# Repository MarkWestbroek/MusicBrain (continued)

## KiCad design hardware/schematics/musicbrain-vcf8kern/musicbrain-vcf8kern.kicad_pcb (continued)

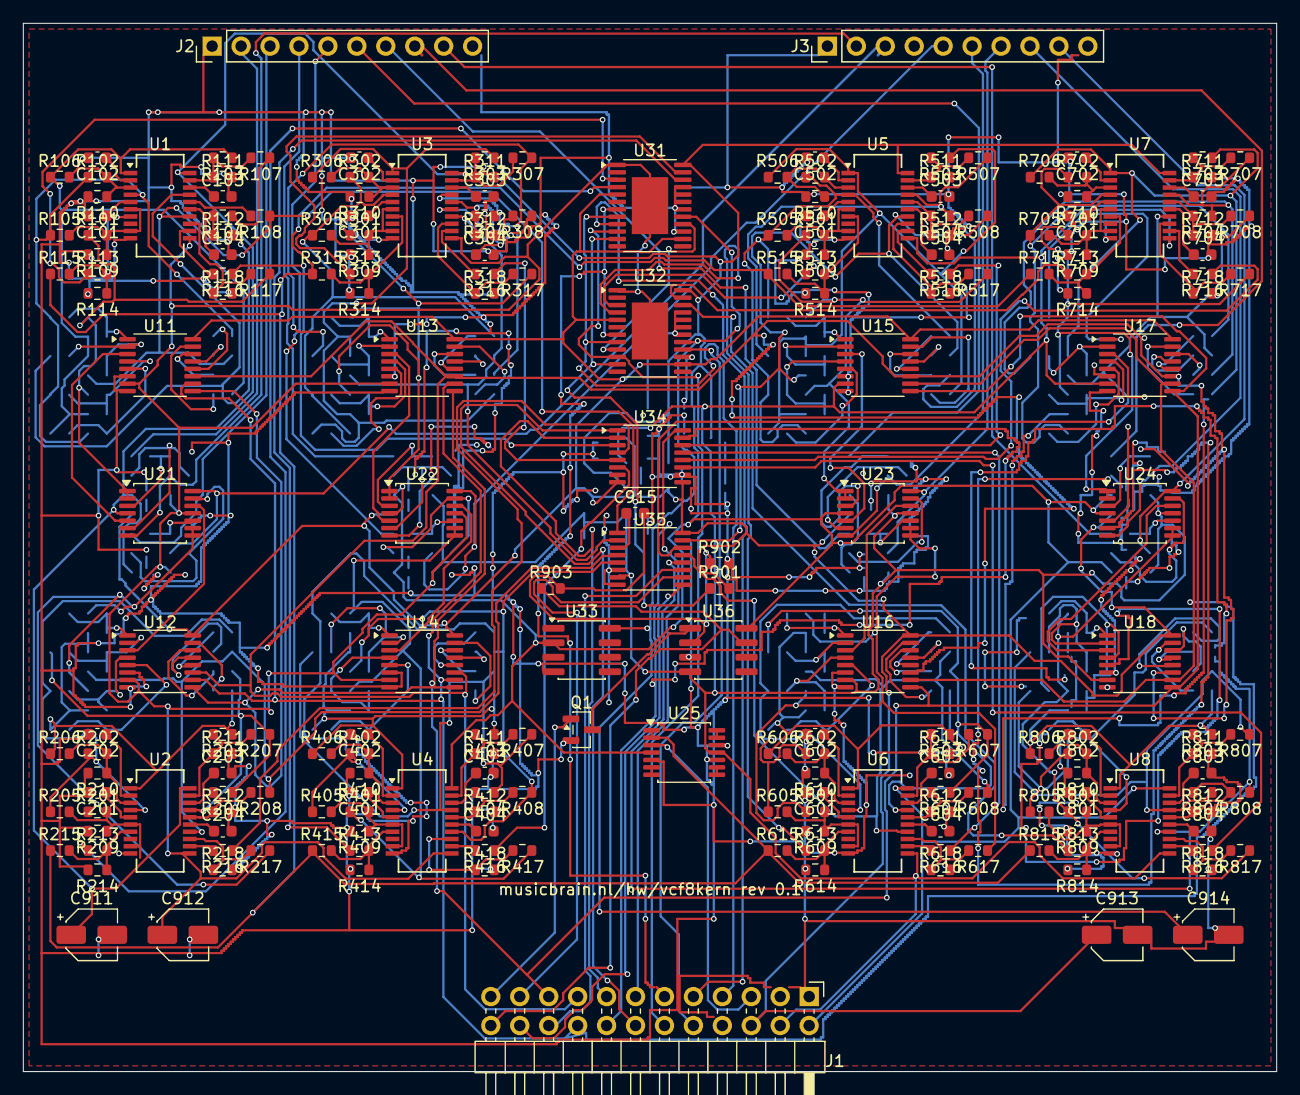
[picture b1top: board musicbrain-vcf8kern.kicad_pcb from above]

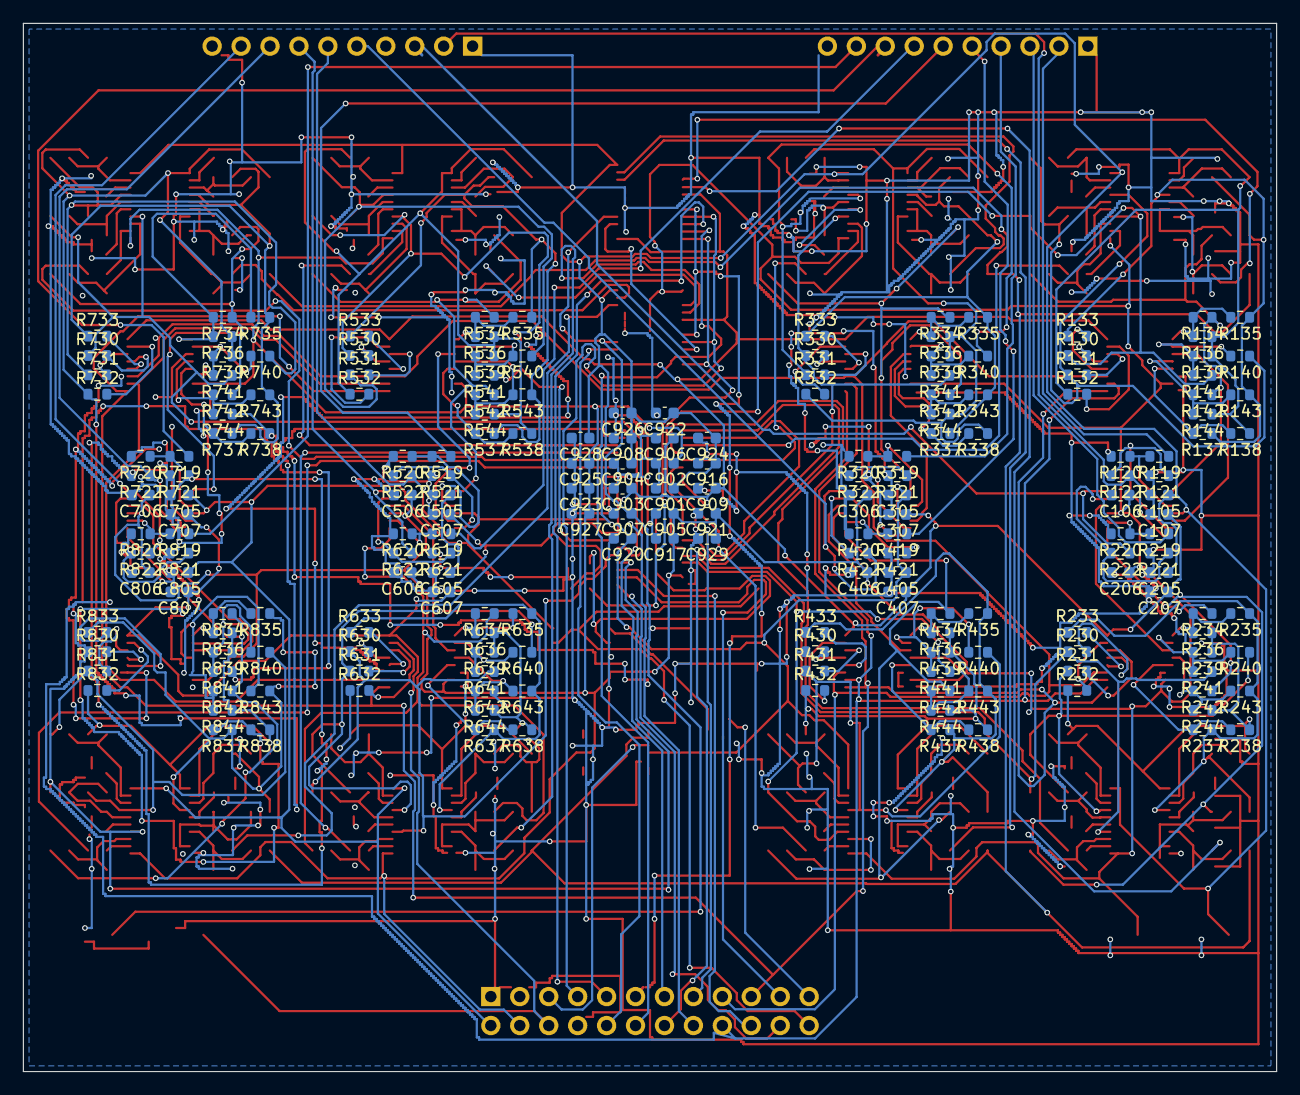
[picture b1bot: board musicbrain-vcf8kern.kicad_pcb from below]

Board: 4 copper layers, 110.0 x 92.0 mm, 412 parts (197 on the bottom side), 280 nets.

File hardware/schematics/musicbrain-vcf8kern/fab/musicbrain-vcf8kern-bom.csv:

"Comment","Designator","Footprint","LCSC Part #"
"1n","C101,C102,C103,C104,C201,C202,C203,C204,C301,C302,C303,C304,C401,C402,C403,C404,C501,C502,C503,C504,C601,C602,C603,C604,C701,C702,C703,C704,C801,C802,C803,C804","C_0603_1608Metric",""
"100n","C105,C106,C107,C205,C206,C207,C305,C306,C307,C405,C406,C407,C505,C506,C507,C605,C606,C607,C705,C706,C707,C805,C806,C807,C901,C902,C903,C904,C905,C906,C907,C908,C909,C916,C917,C920,C921,C922,C923,C924,C925,C926,C927,C928,C929","C_0603_1608Metric",""
"10u","C911,C912,C913,C914","CP_Elec_4x5.3","C3343"
"10n","C915","C_0603_1608Metric",""
"KERNSLOT (2x12)","J1","",""
"AUDIO IN","J2","",""
"AUDIO UIT","J3","",""
"2N7002","Q1","SOT-23",""
"15k","R101,R102,R103,R104,R105,R106,R107,R108,R121,R201,R202,R203,R204,R205,R206,R207,R208,R221,R301,R302,R303,R304,R305,R306,R307,R308,R321,R401,R402,R403,R404,R405,R406,R407,R408,R421,R501,R502,R503,R504,R505,R506,R507,R508,R521,R601,R602,R603,R604,R605,R606,R607,R608,R621,R701,R702,R703,R704,R705,R706,R707,R708,R721,R801,R802,R803,R804,R805,R806,R807,R808,R821","R_0603_1608Metric",""
"200R","R109,R110,R111,R112,R209,R210,R211,R212,R309,R310,R311,R312,R409,R410,R411,R412,R509,R510,R511,R512,R609,R610,R611,R612,R709,R710,R711,R712,R809,R810,R811,R812","R_0603_1608Metric",""
"54.9k","R113,R213,R313,R413,R513,R613,R713,R813","R_0603_1608Metric",""
"1k","R114,R118,R214,R218,R314,R318,R414,R418,R514,R518,R614,R618,R714,R718,R814,R818","R_0603_1608Metric",""
"100k","R115,R215,R315,R415,R515,R615,R715,R815","R_0603_1608Metric",""
"13k","R116,R216,R316,R416,R516,R616,R716,R816","R_0603_1608Metric",""
"16.2k","R117,R217,R317,R417,R517,R617,R717,R817","R_0603_1608Metric",""
"75k","R119,R130,R131,R132,R133,R134,R136,R137,R138,R139,R141,R142,R219,R230,R231,R232,R233,R234,R236,R237,R238,R239,R241,R242,R319,R330,R331,R332,R333,R334,R336,R337,R338,R339,R341,R342,R419,R430,R431,R432,R433,R434,R436,R437,R438,R439,R441,R442,R519,R530,R531,R532,R533,R534,R536,R537,R538,R539,R541,R542,R619,R630,R631,R632,R633,R634,R636,R637,R638,R639,R641,R642,R719,R730,R731,R732,R733,R734,R736,R737,R738,R739,R741,R742,R819,R830,R831,R832,R833,R834,R836,R837,R838,R839,R841,R842","R_0603_1608Metric",""
"18.7k","R120,R220,R320,R420,R520,R620,R720,R820","R_0603_1608Metric",""
"60.4k","R122,R222,R322,R422,R522,R622,R722,R822","R_0603_1608Metric",""
"37.4k","R135,R140,R143,R144,R235,R240,R243,R244,R335,R340,R343,R344,R435,R440,R443,R444,R535,R540,R543,R544,R635,R640,R643,R644,R735,R740,R743,R744,R835,R840,R843,R844","R_0603_1608Metric",""
"10k","R901","R_0603_1608Metric",""
"1M","R902,R903","R_0603_1608Metric",""
"SSI2140","U1,U2,U3,U4,U5,U6,U7,U8","SSOP-20_3.9x8.7mm_P0.635mm",""
"74HC4051","U11,U12,U13,U14,U15,U16,U17,U18,U35","TSSOP-16_4.4x5mm_P0.65mm",""
"TL074","U21,U22,U23,U24,U25","TSSOP-14_4.4x5mm_P0.65mm","C12594"
"AD5754BREZ","U31,U32","HTSSOP-24-1EP_4.4x7.8mm_P0.65mm_EP3.2x5mm","C650230"
"ADR421","U33","SOIC-8_3.9x4.9mm_P1.27mm","C29739"
"DAC128S085CIMTX","U34","TSSOP-16_4.4x5mm_P0.65mm","C882851"
"LM311","U36","SOIC-8_3.9x4.9mm_P1.27mm",""

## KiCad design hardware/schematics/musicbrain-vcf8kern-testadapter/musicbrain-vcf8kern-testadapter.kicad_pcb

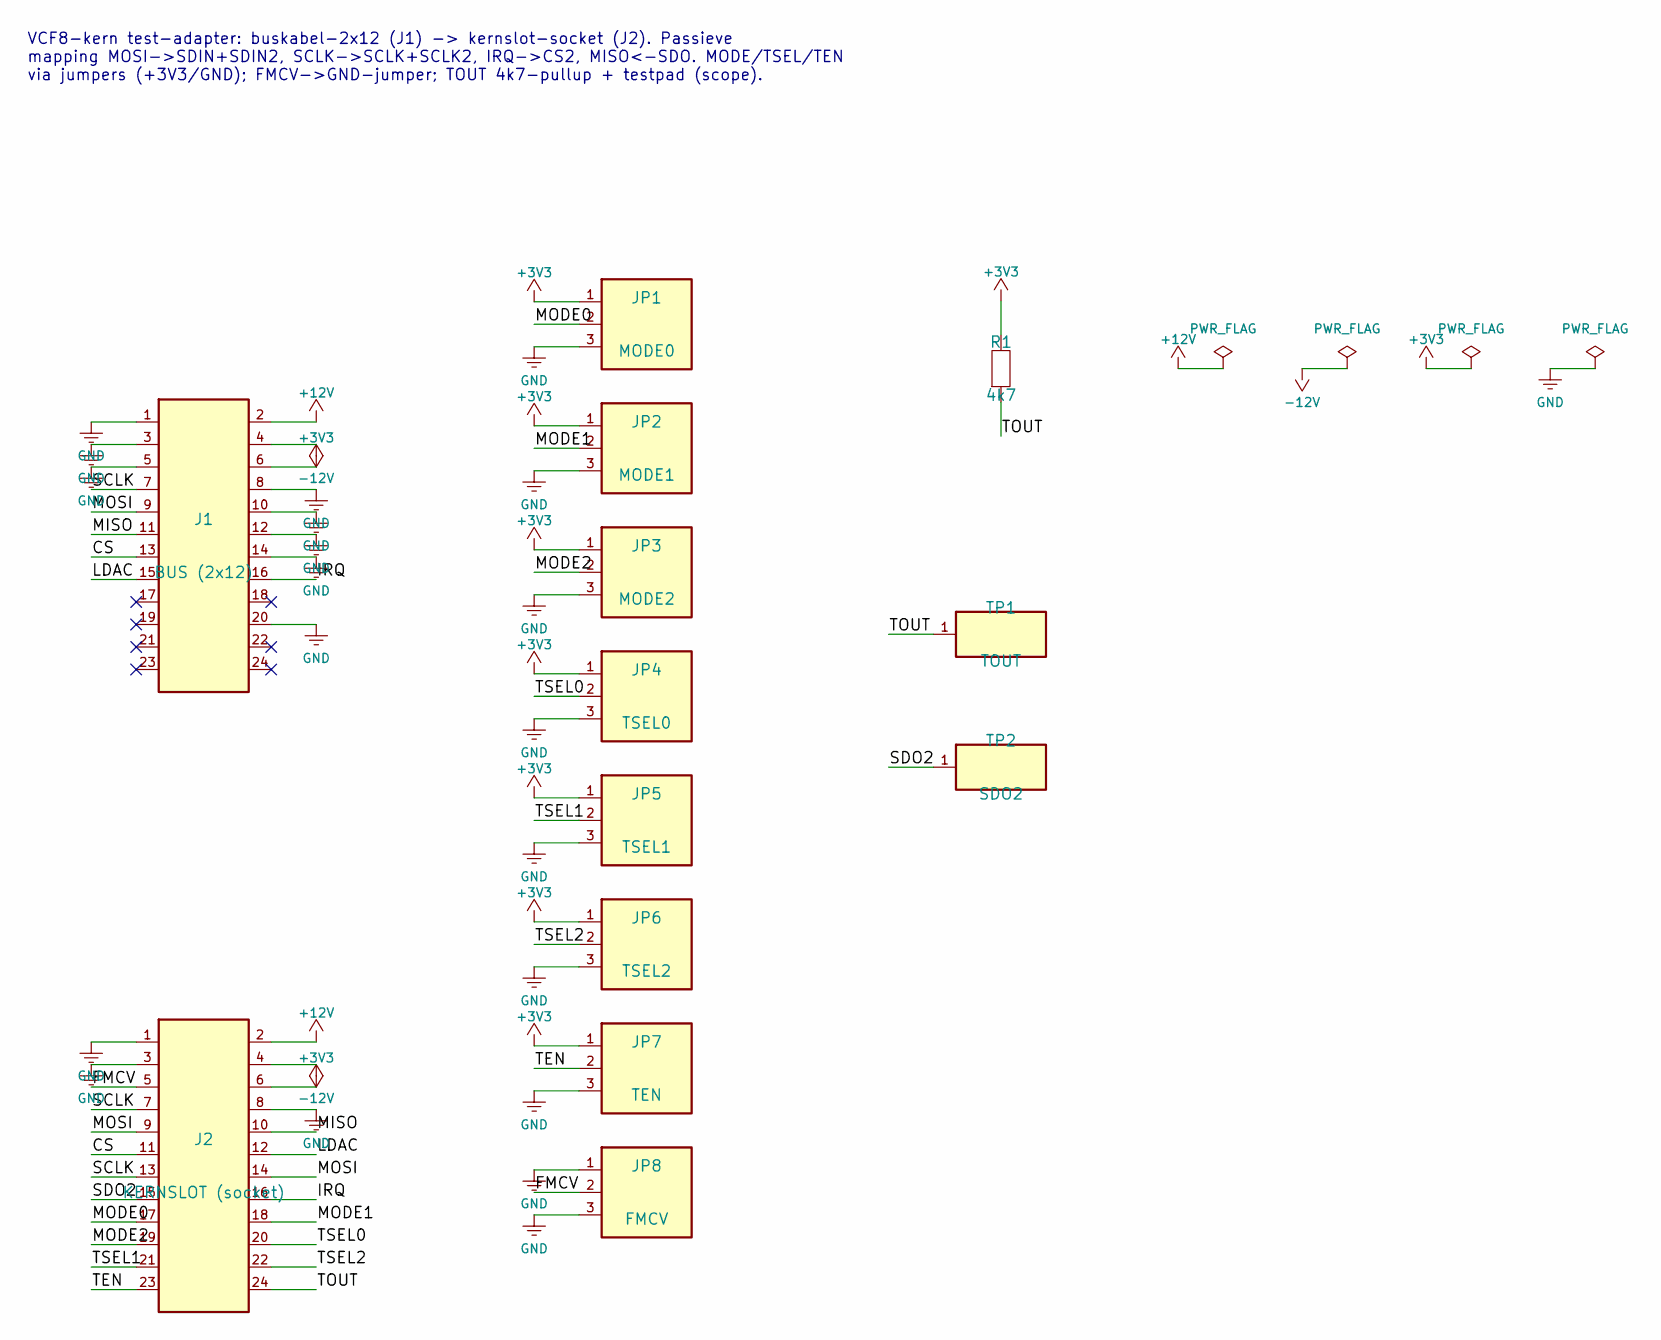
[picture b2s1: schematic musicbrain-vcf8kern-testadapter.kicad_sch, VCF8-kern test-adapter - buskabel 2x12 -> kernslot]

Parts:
J1: BUS (2x12)
J2: KERNSLOT (socket)
JP1: MODE0
JP2: MODE1
JP3: MODE2
JP4: TSEL0
JP5: TSEL1
JP6: TSEL2
JP7: TEN
JP8: FMCV
R1: 4k7; R_0603_1608Metric
TP1: TOUT
TP2: SDO2

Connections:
+3V3: J1.6, J2.6, JP1.1, JP2.1, JP3.1, JP4.1, JP5.1, JP6.1, JP7.1, R1.1
+12V: J1.2, J2.2
-12V: J1.4, J2.4
/CS: J1.13, J2.11
/FMCV: J2.5, JP8.2
/IRQ: J1.16, J2.16
/LDAC: J1.15, J2.12
/MISO: J1.11, J2.10
/MODE0: J2.17, JP1.2
/MODE1: J2.18, JP2.2
/MODE2: J2.19, JP3.2
/MOSI: J1.9, J2.9, J2.14
/SCLK: J1.7, J2.7, J2.13
/SDO2: J2.15, TP2.1
/TEN: J2.23, JP7.2
/TOUT: J2.24, R1.2, TP1.1
/TSEL0: J2.20, JP4.2
/TSEL1: J2.21, JP5.2
/TSEL2: J2.22, JP6.2
GND: J1.1, J1.3, J1.5, J1.8, J1.10, J1.12, J1.14, J1.20, J2.1, J2.3, J2.8, JP1.3, JP2.3, JP3.3, JP4.3, JP5.3, JP6.3, JP7.3, JP8.1, JP8.3

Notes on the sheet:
VCF8-kern test-adapter: buskabel-2x12 (J1) -> kernslot-socket (J2). Passieve mapping MOSI->SDIN+SDIN2, SCLK->SCLK+SCLK2, IRQ->CS2, MISO<-SDO. MODE/TSEL/TEN via jumpers (+3V3/GND); FMCV->GND-jumper; TOUT 4k7-pullup + testpad (scope).

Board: 2 copper layers, 13 parts (0 on the bottom side), 20 nets, no tracks yet.

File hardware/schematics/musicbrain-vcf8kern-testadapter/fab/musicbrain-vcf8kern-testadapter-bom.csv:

"Comment","Designator","Footprint","LCSC Part #"
"BUS (2x12)","J1","",""
"KERNSLOT (socket)","J2","",""
"MODE0","JP1","",""
"MODE1","JP2","",""
"MODE2","JP3","",""
"TSEL0","JP4","",""
"TSEL1","JP5","",""
"TSEL2","JP6","",""
"TEN","JP7","",""
"FMCV","JP8","",""
"4k7","R1","R_0603_1608Metric",""
"TOUT","TP1","",""
"SDO2","TP2","",""

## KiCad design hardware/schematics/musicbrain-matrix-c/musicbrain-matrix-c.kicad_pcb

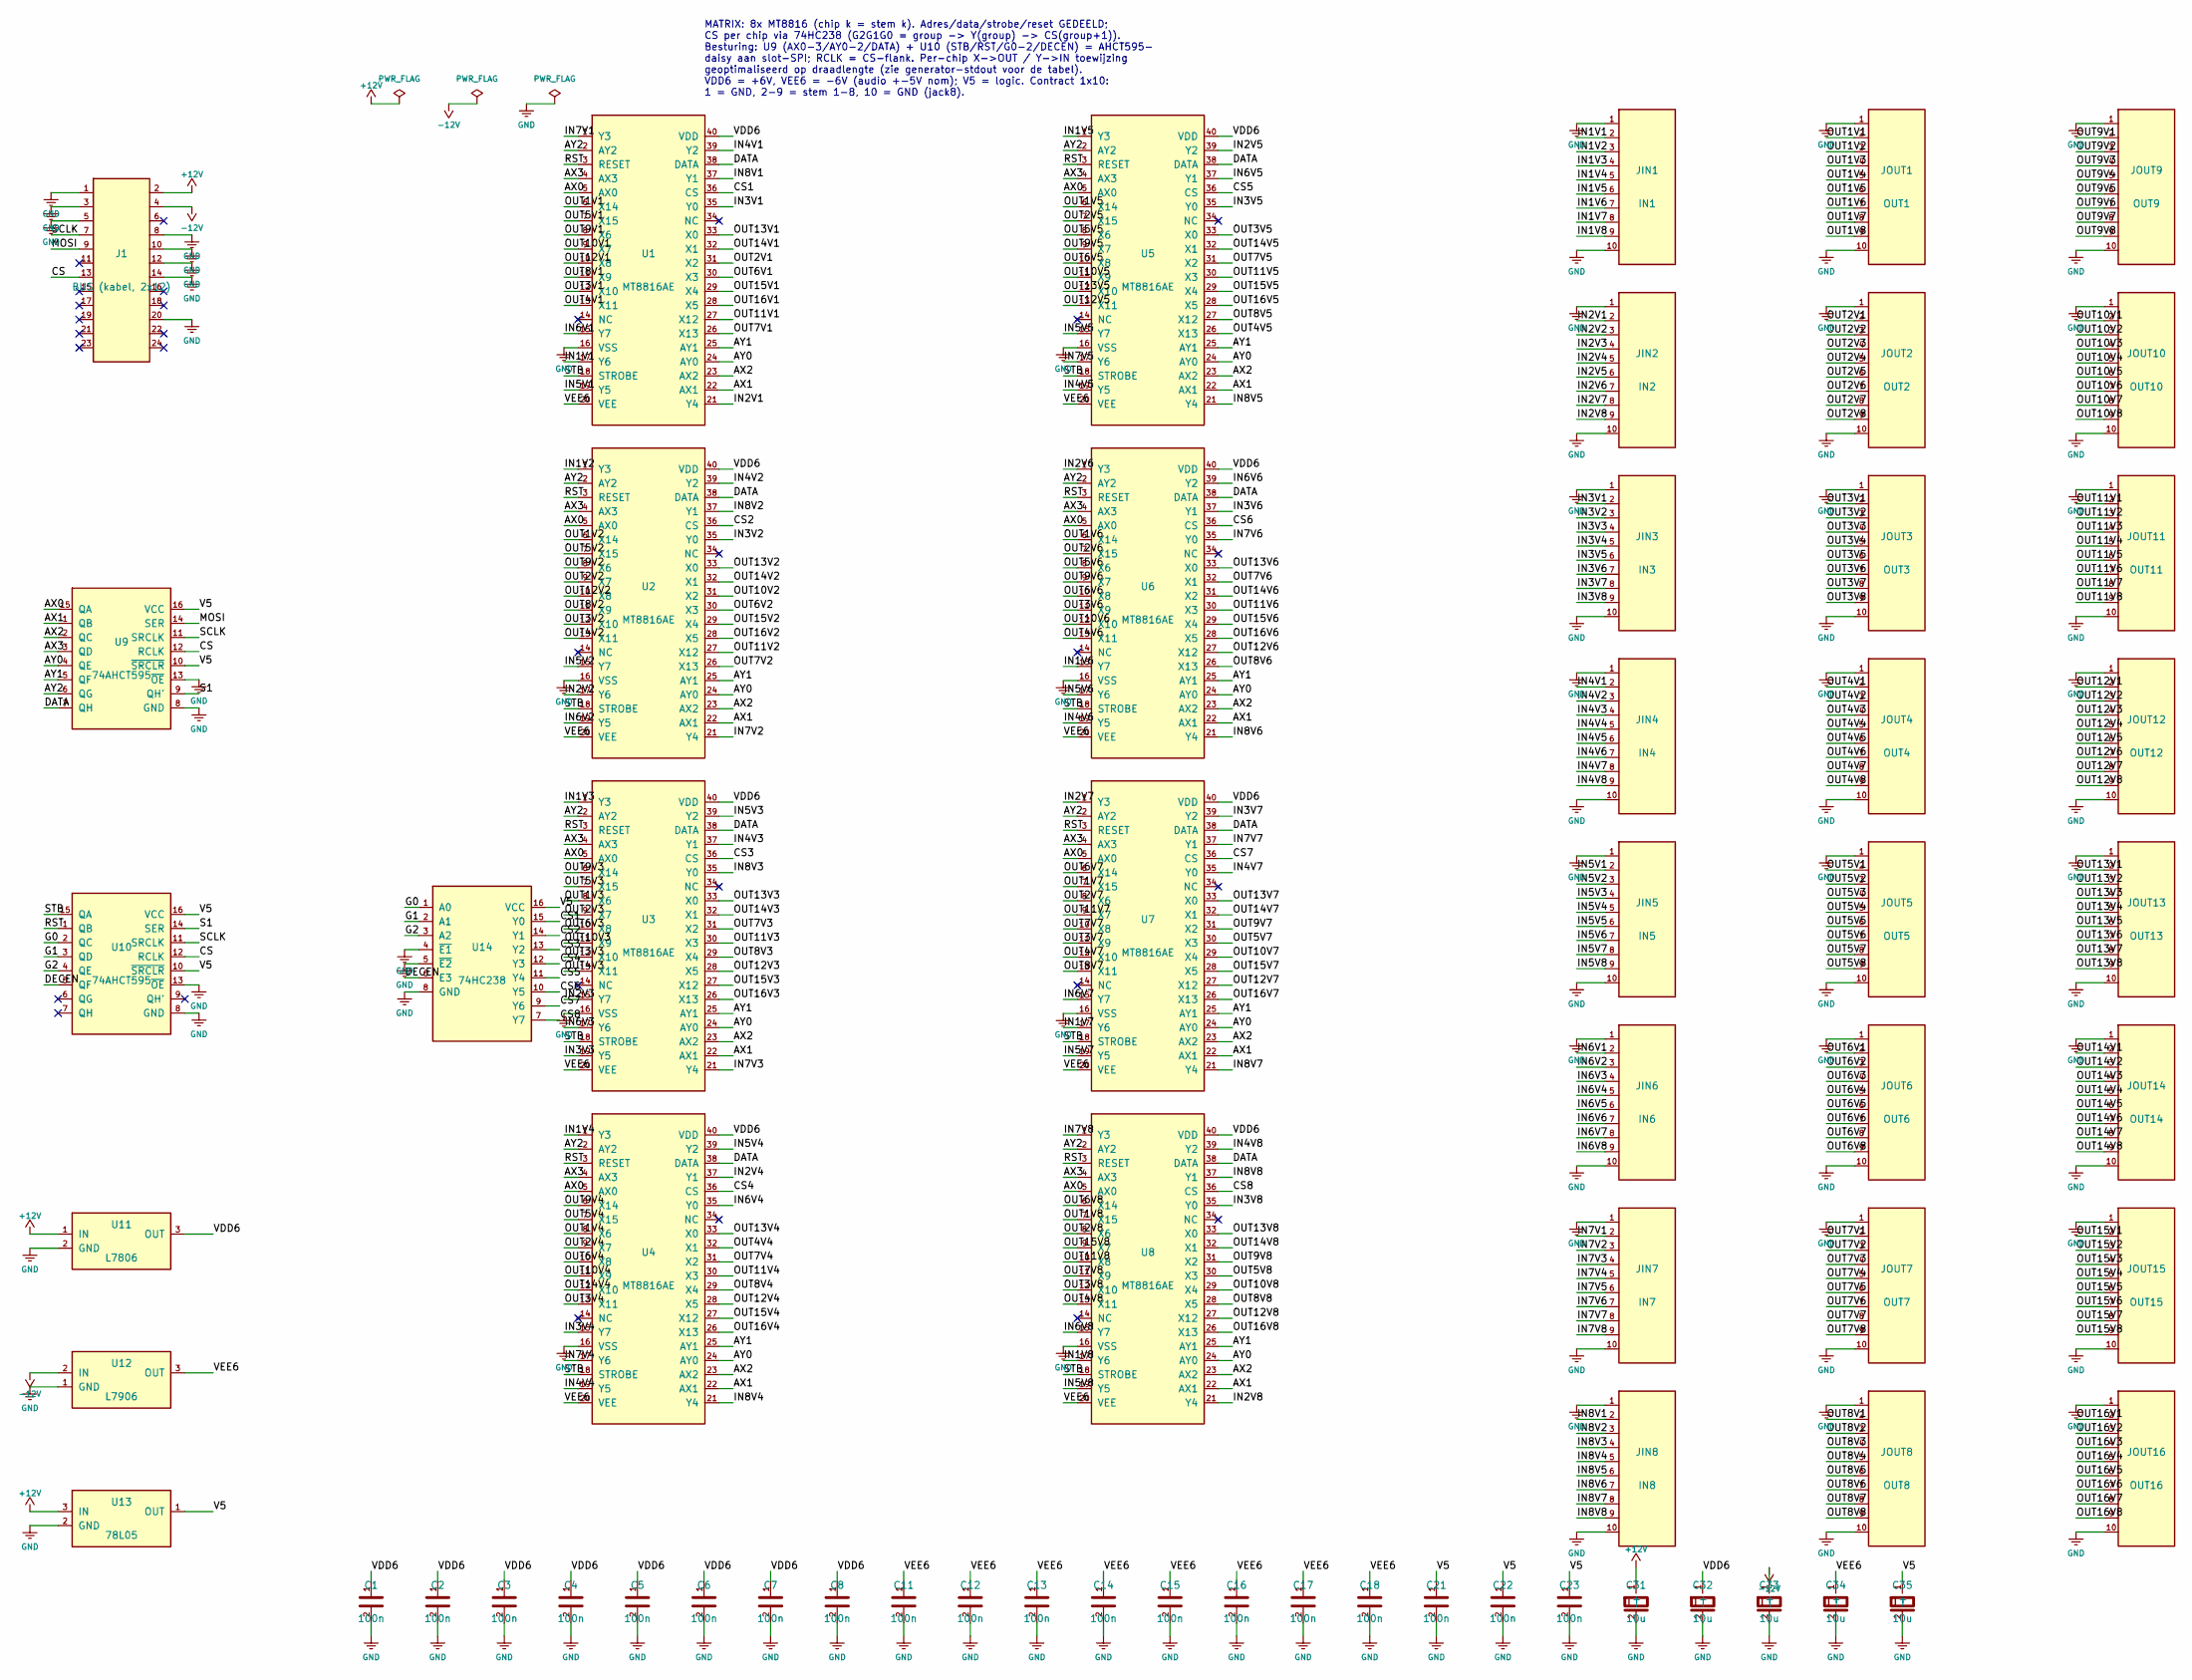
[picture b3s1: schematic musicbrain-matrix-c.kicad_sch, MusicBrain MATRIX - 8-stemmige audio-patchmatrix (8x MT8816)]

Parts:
C1, C2, C3, C4, C5, C6, C7, C8, C11, C12, C13, C14, C15, C16, C17, C18, C21, C22, C23: 100n; C_0805_2012Metric
C31, C32, C33, C34, C35: 10u; CP_Elec_4x5.3
J1: BUS (kabel, 2x12); PinSocket_2x12_P2.54mm_Vertical
JIN1: IN1; PinHeader_1x10_P2.54mm_Vertical
JIN2: IN2; PinHeader_1x10_P2.54mm_Vertical
JIN3: IN3; PinHeader_1x10_P2.54mm_Vertical
JIN4: IN4; PinHeader_1x10_P2.54mm_Vertical
JIN5: IN5; PinHeader_1x10_P2.54mm_Vertical
JIN6: IN6; PinHeader_1x10_P2.54mm_Vertical
JIN7: IN7; PinHeader_1x10_P2.54mm_Vertical
JIN8: IN8; PinHeader_1x10_P2.54mm_Vertical
JOUT1: OUT1; PinHeader_1x10_P2.54mm_Vertical
JOUT2: OUT2; PinHeader_1x10_P2.54mm_Vertical
JOUT3: OUT3; PinHeader_1x10_P2.54mm_Vertical
JOUT4: OUT4; PinHeader_1x10_P2.54mm_Vertical
JOUT5: OUT5; PinHeader_1x10_P2.54mm_Vertical
JOUT6: OUT6; PinHeader_1x10_P2.54mm_Vertical
JOUT7: OUT7; PinHeader_1x10_P2.54mm_Vertical
JOUT8: OUT8; PinHeader_1x10_P2.54mm_Vertical
JOUT9: OUT9; PinHeader_1x10_P2.54mm_Vertical
JOUT10: OUT10; PinHeader_1x10_P2.54mm_Vertical
JOUT11: OUT11; PinHeader_1x10_P2.54mm_Vertical
JOUT12: OUT12; PinHeader_1x10_P2.54mm_Vertical
JOUT13: OUT13; PinHeader_1x10_P2.54mm_Vertical
JOUT14: OUT14; PinHeader_1x10_P2.54mm_Vertical
JOUT15: OUT15; PinHeader_1x10_P2.54mm_Vertical
JOUT16: OUT16; PinHeader_1x10_P2.54mm_Vertical
U1, U2, U3, U4, U5, U6, U7, U8: MT8816AE; DIP-40_W15.24mm
U9, U10: 74AHCT595; SOIC-16_3.9x9.9mm_P1.27mm
U11: L7806; TO-220-3_Vertical
U12: L7906; TO-220-3_Vertical
U13: 78L05; TO-92_Inline
U14: 74HC238; SOIC-16_3.9x9.9mm_P1.27mm

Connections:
+12V: C31.1 (+), J1.2, U11.1 (IN), U13.3 (IN)
-12V: C33.1 (+), J1.4, U12.2 (IN)
/AX0: U1.5 (AX0), U2.5 (AX0), U3.5 (AX0), U4.5 (AX0), U5.5 (AX0), U6.5 (AX0), U7.5 (AX0), U8.5 (AX0), U9.15 (QA)
/AX1: U1.22 (AX1), U2.22 (AX1), U3.22 (AX1), U4.22 (AX1), U5.22 (AX1), U6.22 (AX1), U7.22 (AX1), U8.22 (AX1), U9.1 (QB)
/AX2: U1.23 (AX2), U2.23 (AX2), U3.23 (AX2), U4.23 (AX2), U5.23 (AX2), U6.23 (AX2), U7.23 (AX2), U8.23 (AX2), U9.2 (QC)
/AX3: U1.4 (AX3), U2.4 (AX3), U3.4 (AX3), U4.4 (AX3), U5.4 (AX3), U6.4 (AX3), U7.4 (AX3), U8.4 (AX3), U9.3 (QD)
/AY0: U1.24 (AY0), U2.24 (AY0), U3.24 (AY0), U4.24 (AY0), U5.24 (AY0), U6.24 (AY0), U7.24 (AY0), U8.24 (AY0), U9.4 (QE)
/AY1: U1.25 (AY1), U2.25 (AY1), U3.25 (AY1), U4.25 (AY1), U5.25 (AY1), U6.25 (AY1), U7.25 (AY1), U8.25 (AY1), U9.5 (QF)
/AY2: U1.2 (AY2), U2.2 (AY2), U3.2 (AY2), U4.2 (AY2), U5.2 (AY2), U6.2 (AY2), U7.2 (AY2), U8.2 (AY2), U9.6 (QG)
/CS: J1.13, U9.12 (RCLK), U10.12 (RCLK)
/CS1: U1.36 (CS), U14.15 (Y0)
/CS2: U2.36 (CS), U14.14 (Y1)
/CS3: U3.36 (CS), U14.13 (Y2)
/CS4: U4.36 (CS), U14.12 (Y3)
/CS5: U5.36 (CS), U14.11 (Y4)
/CS6: U6.36 (CS), U14.10 (Y5)
/CS7: U7.36 (CS), U14.9 (Y6)
/CS8: U8.36 (CS), U14.7 (Y7)
/DATA: U1.38 (DATA), U2.38 (DATA), U3.38 (DATA), U4.38 (DATA), U5.38 (DATA), U6.38 (DATA), U7.38 (DATA), U8.38 (DATA), U9.7 (QH)
/DECEN: U10.5 (QF), U14.6 (E3)
/G0: U10.2 (QC), U14.1 (A0)
/G1: U10.3 (QD), U14.2 (A1)
/G2: U10.4 (QE), U14.3 (A2)
/IN1V1: JIN1.2, U1.17 (Y6)
/IN1V2: JIN1.3, U2.1 (Y3)
/IN1V3: JIN1.4, U3.1 (Y3)
/IN1V4: JIN1.5, U4.1 (Y3)
/IN1V5: JIN1.6, U5.1 (Y3)
/IN1V6: JIN1.7, U6.15 (Y7)
/IN1V7: JIN1.8, U7.17 (Y6)
/IN1V8: JIN1.9, U8.17 (Y6)
/IN2V1: JIN2.2, U1.21 (Y4)
/IN2V2: JIN2.3, U2.17 (Y6)
/IN2V3: JIN2.4, U3.15 (Y7)
/IN2V4: JIN2.5, U4.37 (Y1)
/IN2V5: JIN2.6, U5.39 (Y2)
/IN2V6: JIN2.7, U6.1 (Y3)
/IN2V7: JIN2.8, U7.1 (Y3)
/IN2V8: JIN2.9, U8.21 (Y4)
/IN3V1: JIN3.2, U1.35 (Y0)
/IN3V2: JIN3.3, U2.35 (Y0)
/IN3V3: JIN3.4, U3.19 (Y5)
/IN3V4: JIN3.5, U4.15 (Y7)
/IN3V5: JIN3.6, U5.35 (Y0)
/IN3V6: JIN3.7, U6.37 (Y1)
/IN3V7: JIN3.8, U7.39 (Y2)
/IN3V8: JIN3.9, U8.35 (Y0)
/IN4V1: JIN4.2, U1.39 (Y2)
/IN4V2: JIN4.3, U2.39 (Y2)
/IN4V3: JIN4.4, U3.37 (Y1)
/IN4V4: JIN4.5, U4.19 (Y5)
/IN4V5: JIN4.6, U5.19 (Y5)
/IN4V6: JIN4.7, U6.19 (Y5)
/IN4V7: JIN4.8, U7.35 (Y0)
/IN4V8: JIN4.9, U8.39 (Y2)
/IN5V1: JIN5.2, U1.19 (Y5)
/IN5V2: JIN5.3, U2.15 (Y7)
/IN5V3: JIN5.4, U3.39 (Y2)
/IN5V4: JIN5.5, U4.39 (Y2)
/IN5V5: JIN5.6, U5.15 (Y7)
/IN5V6: JIN5.7, U6.17 (Y6)
/IN5V7: JIN5.8, U7.19 (Y5)
/IN5V8: JIN5.9, U8.19 (Y5)
/IN6V1: JIN6.2, U1.15 (Y7)
/IN6V2: JIN6.3, U2.19 (Y5)
/IN6V3: JIN6.4, U3.17 (Y6)
/IN6V4: JIN6.5, U4.35 (Y0)
/IN6V5: JIN6.6, U5.37 (Y1)
/IN6V6: JIN6.7, U6.39 (Y2)
/IN6V7: JIN6.8, U7.15 (Y7)
/IN6V8: JIN6.9, U8.15 (Y7)
/IN7V1: JIN7.2, U1.1 (Y3)
/IN7V2: JIN7.3, U2.21 (Y4)
/IN7V3: JIN7.4, U3.21 (Y4)
/IN7V4: JIN7.5, U4.17 (Y6)
/IN7V5: JIN7.6, U5.17 (Y6)
/IN7V6: JIN7.7, U6.35 (Y0)
/IN7V7: JIN7.8, U7.37 (Y1)
/IN7V8: JIN7.9, U8.1 (Y3)
/IN8V1: JIN8.2, U1.37 (Y1)
/IN8V2: JIN8.3, U2.37 (Y1)
/IN8V3: JIN8.4, U3.35 (Y0)
/IN8V4: JIN8.5, U4.21 (Y4)
/IN8V5: JIN8.6, U5.21 (Y4)
/IN8V6: JIN8.7, U6.21 (Y4)
/IN8V7: JIN8.8, U7.21 (Y4)
/IN8V8: JIN8.9, U8.37 (Y1)
/MOSI: J1.9, U9.14 (SER)
/OUT1V1: JOUT1.2, U1.6 (X14)
/OUT1V2: JOUT1.3, U2.6 (X14)
/OUT1V3: JOUT1.4, U3.8 (X6)
/OUT1V4: JOUT1.5, U4.8 (X6)
/OUT1V5: JOUT1.6, U5.6 (X14)
/OUT1V6: JOUT1.7, U6.6 (X14)
/OUT1V7: JOUT1.8, U7.7 (X15)
/OUT1V8: JOUT1.9, U8.7 (X15)
/OUT2V1: JOUT2.2, U1.31 (X2)
/OUT2V2: JOUT2.3, U2.9 (X7)
/OUT2V3: JOUT2.4, U3.9 (X7)
/OUT2V4: JOUT2.5, U4.9 (X7)
/OUT2V5: JOUT2.6, U5.7 (X15)
/OUT2V6: JOUT2.7, U6.7 (X15)
/OUT2V7: JOUT2.8, U7.8 (X6)
/OUT2V8: JOUT2.9, U8.8 (X6)
/OUT3V1: JOUT3.2, U1.12 (X10)
/OUT3V2: JOUT3.3, U2.12 (X10)
/OUT3V3: JOUT3.4, U3.12 (X10)
/OUT3V4: JOUT3.5, U4.13 (X11)
/OUT3V5: JOUT3.6, U5.33 (X0)
/OUT3V6: JOUT3.7, U6.11 (X9)
/OUT3V7: JOUT3.8, U7.11 (X9)
/OUT3V8: JOUT3.9, U8.12 (X10)
/OUT4V1: JOUT4.2, U1.13 (X11)
/OUT4V2: JOUT4.3, U2.13 (X11)
/OUT4V3: JOUT4.4, U3.13 (X11)
/OUT4V4: JOUT4.5, U4.32 (X1)
/OUT4V5: JOUT4.6, U5.26 (X13)
/OUT4V6: JOUT4.7, U6.13 (X11)
/OUT4V7: JOUT4.8, U7.12 (X10)
/OUT4V8: JOUT4.9, U8.13 (X11)
/OUT5V1: JOUT5.2, U1.7 (X15)
/OUT5V2: JOUT5.3, U2.7 (X15)
/OUT5V3: JOUT5.4, U3.7 (X15)
/OUT5V4: JOUT5.5, U4.7 (X15)
/OUT5V5: JOUT5.6, U5.8 (X6)
/OUT5V6: JOUT5.7, U6.8 (X6)
/OUT5V7: JOUT5.8, U7.30 (X3)
/OUT5V8: JOUT5.9, U8.30 (X3)
/OUT6V1: JOUT6.2, U1.30 (X3)
/OUT6V2: JOUT6.3, U2.30 (X3)
/OUT6V3: JOUT6.4, U3.10 (X8)
/OUT6V4: JOUT6.5, U4.10 (X8)
/OUT6V5: JOUT6.6, U5.10 (X8)
/OUT6V6: JOUT6.7, U6.10 (X8)
/OUT6V7: JOUT6.8, U7.6 (X14)
/OUT6V8: JOUT6.9, U8.6 (X14)
/OUT7V1: JOUT7.2, U1.26 (X13)
/OUT7V2: JOUT7.3, U2.26 (X13)
/OUT7V3: JOUT7.4, U3.31 (X2)
/OUT7V4: JOUT7.5, U4.31 (X2)
/OUT7V5: JOUT7.6, U5.31 (X2)
/OUT7V6: JOUT7.7, U6.32 (X1)
/OUT7V7: JOUT7.8, U7.10 (X8)
/OUT7V8: JOUT7.9, U8.11 (X9)
/OUT8V1: JOUT8.2, U1.11 (X9)
/OUT8V2: JOUT8.3, U2.11 (X9)
/OUT8V3: JOUT8.4, U3.29 (X4)
/OUT8V4: JOUT8.5, U4.29 (X4)
/OUT8V5: JOUT8.6, U5.27 (X12)
/OUT8V6: JOUT8.7, U6.26 (X13)
/OUT8V7: JOUT8.8, U7.13 (X11)
/OUT8V8: JOUT8.9, U8.28 (X5)
/OUT9V1: JOUT9.2, U1.8 (X6)
/OUT9V2: JOUT9.3, U2.8 (X6)
/OUT9V3: JOUT9.4, U3.6 (X14)
/OUT9V4: JOUT9.5, U4.6 (X14)
/OUT9V5: JOUT9.6, U5.9 (X7)
/OUT9V6: JOUT9.7, U6.9 (X7)
/OUT9V7: JOUT9.8, U7.31 (X2)
/OUT9V8: JOUT9.9, U8.31 (X2)
/OUT10V1: JOUT10.2, U1.9 (X7)
/OUT10V2: JOUT10.3, U2.31 (X2)
/OUT10V3: JOUT10.4, U3.11 (X9)
/OUT10V4: JOUT10.5, U4.11 (X9)
/OUT10V5: JOUT10.6, U5.11 (X9)
/OUT10V6: JOUT10.7, U6.12 (X10)
/OUT10V7: JOUT10.8, U7.29 (X4)
/OUT10V8: JOUT10.9, U8.29 (X4)
/OUT11V1: JOUT11.2, U1.27 (X12)
/OUT11V2: JOUT11.3, U2.27 (X12)
/OUT11V3: JOUT11.4, U3.30 (X3)
/OUT11V4: JOUT11.5, U4.30 (X3)
/OUT11V5: JOUT11.6, U5.30 (X3)
/OUT11V6: JOUT11.7, U6.30 (X3)
/OUT11V7: JOUT11.8, U7.9 (X7)
/OUT11V8: JOUT11.9, U8.10 (X8)
/OUT12V1: JOUT12.2, U1.10 (X8)
/OUT12V2: JOUT12.3, U2.10 (X8)
/OUT12V3: JOUT12.4, U3.28 (X5)
/OUT12V4: JOUT12.5, U4.28 (X5)
/OUT12V5: JOUT12.6, U5.13 (X11)
/OUT12V6: JOUT12.7, U6.27 (X12)
/OUT12V7: JOUT12.8, U7.27 (X12)
/OUT12V8: JOUT12.9, U8.27 (X12)
/OUT13V1: JOUT13.2, U1.33 (X0)
/OUT13V2: JOUT13.3, U2.33 (X0)
/OUT13V3: JOUT13.4, U3.33 (X0)
/OUT13V4: JOUT13.5, U4.33 (X0)
/OUT13V5: JOUT13.6, U5.12 (X10)
/OUT13V6: JOUT13.7, U6.33 (X0)
/OUT13V7: JOUT13.8, U7.33 (X0)
/OUT13V8: JOUT13.9, U8.33 (X0)
/OUT14V1: JOUT14.2, U1.32 (X1)
/OUT14V2: JOUT14.3, U2.32 (X1)
/OUT14V3: JOUT14.4, U3.32 (X1)
/OUT14V4: JOUT14.5, U4.12 (X10)
/OUT14V5: JOUT14.6, U5.32 (X1)
/OUT14V6: JOUT14.7, U6.31 (X2)
/OUT14V7: JOUT14.8, U7.32 (X1)
/OUT14V8: JOUT14.9, U8.32 (X1)
/OUT15V1: JOUT15.2, U1.29 (X4)
/OUT15V2: JOUT15.3, U2.29 (X4)
/OUT15V3: JOUT15.4, U3.27 (X12)
/OUT15V4: JOUT15.5, U4.27 (X12)
/OUT15V5: JOUT15.6, U5.29 (X4)
/OUT15V6: JOUT15.7, U6.29 (X4)
/OUT15V7: JOUT15.8, U7.28 (X5)
/OUT15V8: JOUT15.9, U8.9 (X7)
/OUT16V1: JOUT16.2, U1.28 (X5)
/OUT16V2: JOUT16.3, U2.28 (X5)
/OUT16V3: JOUT16.4, U3.26 (X13)
/OUT16V4: JOUT16.5, U4.26 (X13)
/OUT16V5: JOUT16.6, U5.28 (X5)
/OUT16V6: JOUT16.7, U6.28 (X5)
/OUT16V7: JOUT16.8, U7.26 (X13)
/OUT16V8: JOUT16.9, U8.26 (X13)
/RST: U1.3 (RESET), U2.3 (RESET), U3.3 (RESET), U4.3 (RESET), U5.3 (RESET), U6.3 (RESET), U7.3 (RESET), U8.3 (RESET), U10.1 (QB)
/S1: U9.9 (QH'), U10.14 (SER)
/SCLK: J1.7, U9.11 (SRCLK), U10.11 (SRCLK)
/STB: U1.18 (STROBE), U2.18 (STROBE), U3.18 (STROBE), U4.18 (STROBE), U5.18 (STROBE), U6.18 (STROBE), U7.18 (STROBE), U8.18 (STROBE), U10.15 (QA)
/V5: C21.1, C22.1, C23.1, C35.1 (+), U9.10 (~SRCLR), U9.16 (VCC), U10.10 (~SRCLR), U10.16 (VCC), U13.1 (OUT), U14.16 (VCC)
/VDD6: C1.1, C2.1, C3.1, C4.1, C5.1, C6.1, C7.1, C8.1, C32.1 (+), U1.40 (VDD), U2.40 (VDD), U3.40 (VDD), U4.40 (VDD), U5.40 (VDD), U6.40 (VDD), U7.40 (VDD), U8.40 (VDD), U11.3 (OUT)
/VEE6: C11.1, C12.1, C13.1, C14.1, C15.1, C16.1, C17.1, C18.1, C34.1 (+), U1.20 (VEE), U2.20 (VEE), U3.20 (VEE), U4.20 (VEE), U5.20 (VEE), U6.20 (VEE), U7.20 (VEE), U8.20 (VEE), U12.3 (OUT)
GND: C1.2, C2.2, C3.2, C4.2, C5.2, C6.2, C7.2, C8.2, C11.2, C12.2, C13.2, C14.2, C15.2, C16.2, C17.2, C18.2, C21.2, C22.2, C23.2, C31.2 (-), C32.2 (-), C33.2 (-), C34.2 (-), C35.2 (-), J1.1, J1.3, J1.5, J1.8, J1.10, J1.12, J1.14, J1.20, JIN1.1, JIN1.10, JIN2.1, JIN2.10, JIN3.1, JIN3.10, JIN4.1, JIN4.10, JIN5.1, JIN5.10, JIN6.1, JIN6.10, JIN7.1, JIN7.10, JIN8.1, JIN8.10, JOUT1.1, JOUT1.10, JOUT2.1, JOUT2.10, JOUT3.1, JOUT3.10, JOUT4.1, JOUT4.10, JOUT5.1, JOUT5.10, JOUT6.1, JOUT6.10, JOUT7.1, JOUT7.10, JOUT8.1, JOUT8.10, JOUT9.1, JOUT9.10, JOUT10.1, JOUT10.10, JOUT11.1, JOUT11.10, JOUT12.1, JOUT12.10, JOUT13.1, JOUT13.10, JOUT14.1, JOUT14.10, JOUT15.1, JOUT15.10, JOUT16.1, JOUT16.10, U1.16 (VSS), U2.16 (VSS), U3.16 (VSS), U4.16 (VSS), U5.16 (VSS), U6.16 (VSS), U7.16 (VSS), U8.16 (VSS), U9.8 (GND), U9.13 (~OE), U10.8 (GND), U10.13 (~OE), U11.2 (GND), U12.1 (GND), U13.2 (GND), U14.4 (~E1), U14.5 (~E2), U14.8 (GND)

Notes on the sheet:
MATRIX: 8x MT8816 (chip k = stem k). Adres/data/strobe/reset GEDEELD; CS per chip via 74HC238 (G2G1G0 = group -> Y(group) -> CS(group+1)). Besturing: U9 (AX0-3/AY0-2/DATA) + U10 (STB/RST/G0-2/DECEN) = AHCT595- daisy aan slot-SPI; RCLK = CS-flank. Per-chip X->OUT / Y->IN toewijzing geoptimaliseerd o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

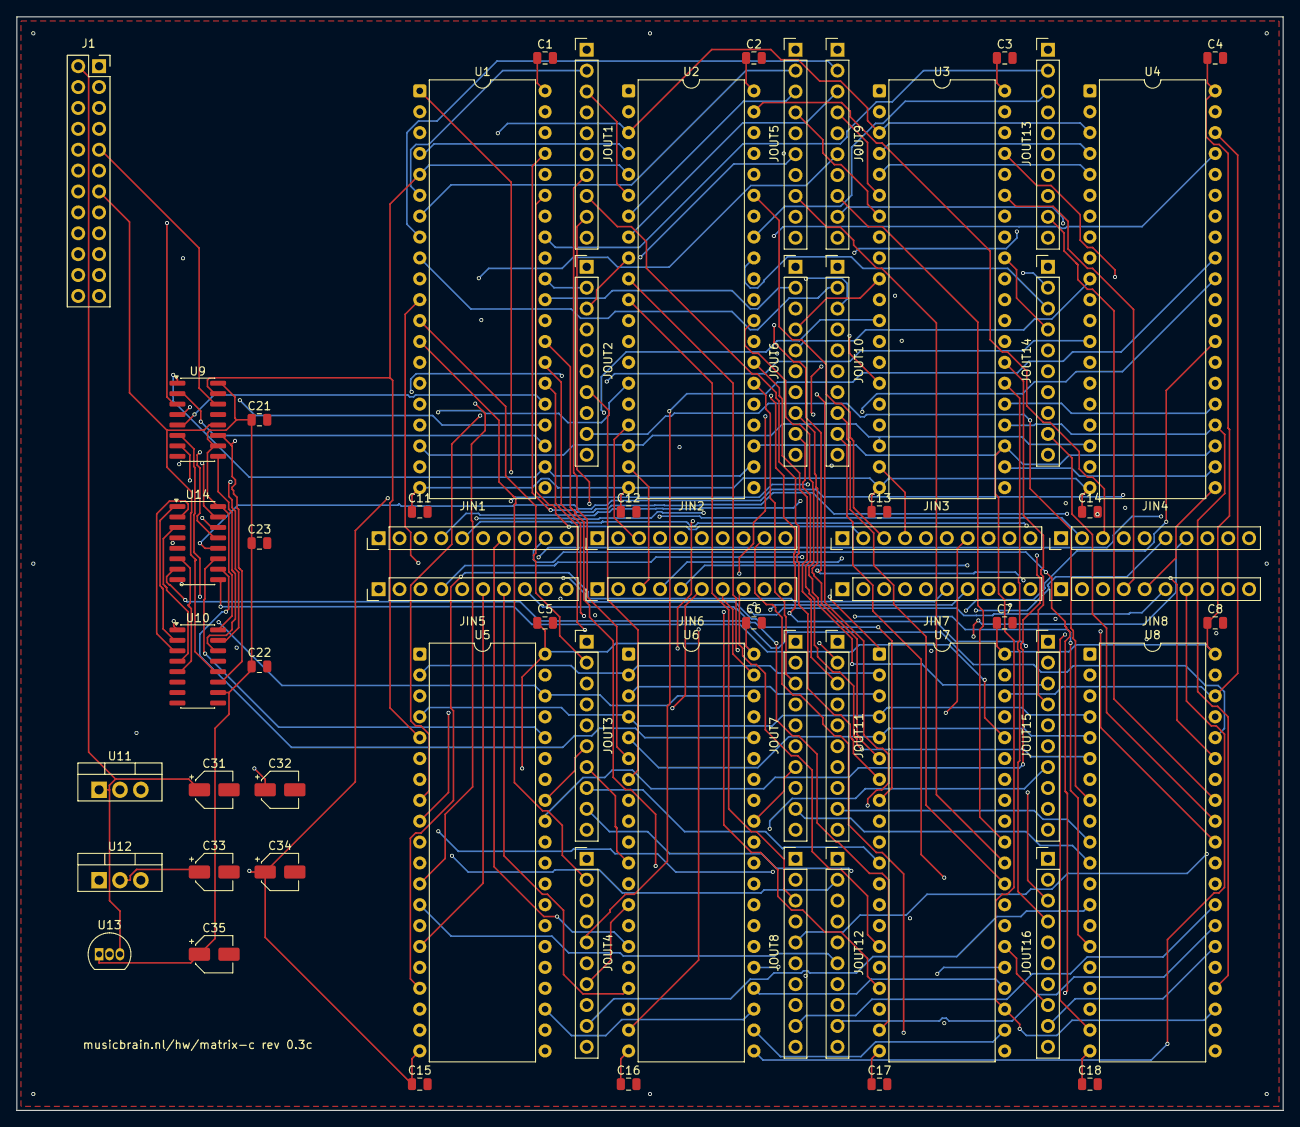
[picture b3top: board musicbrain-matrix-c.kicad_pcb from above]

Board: 4 copper layers, 154.0 x 133.0 mm, 63 parts (0 on the bottom side), 224 nets.

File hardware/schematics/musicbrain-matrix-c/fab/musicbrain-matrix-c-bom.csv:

"Comment","Designator","Footprint","LCSC Part #"
"100n","C1,C2,C3,C4,C5,C6,C7,C8,C11,C12,C13,C14,C15,C16,C17,C18,C21,C22,C23","C_0805_2012Metric","C49678"
"10u","C31,C32,C33,C34,C35","CP_Elec_4x5.3","C3343"
"BUS (kabel, 2x12)","J1","PinSocket_2x12_P2.54mm_Vertical","C22373917"
"IN/OUT","JIN1,JIN2,JIN3,JIN4,JIN5,JIN6,JIN7,JIN8,JOUT1,JOUT2,JOUT3,JOUT4,JOUT5,JOUT6,JOUT7,JOUT8,JOUT9,JOUT10,JOUT11,JOUT12,JOUT13,JOUT14,JOUT15,JOUT16","PinHeader_1x10_P2.54mm_Vertical","C19190976"
"MT8816AE","U1,U2,U3,U4,U5,U6,U7,U8","DIP-40_W15.24mm","C72123"
"74AHCT595","U9,U10","SOIC-16_3.9x9.9mm_P1.27mm","C126402"
"L7806","U11","TO-220-3_Vertical",""
"L7906","U12","TO-220-3_Vertical",""
"78L05","U13","TO-92_Inline",""
"74HC238","U14","SOIC-16_3.9x9.9mm_P1.27mm","C5620"
